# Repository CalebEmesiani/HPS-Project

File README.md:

# HPS-Project
 My project for the Google Hardware Product Sprint

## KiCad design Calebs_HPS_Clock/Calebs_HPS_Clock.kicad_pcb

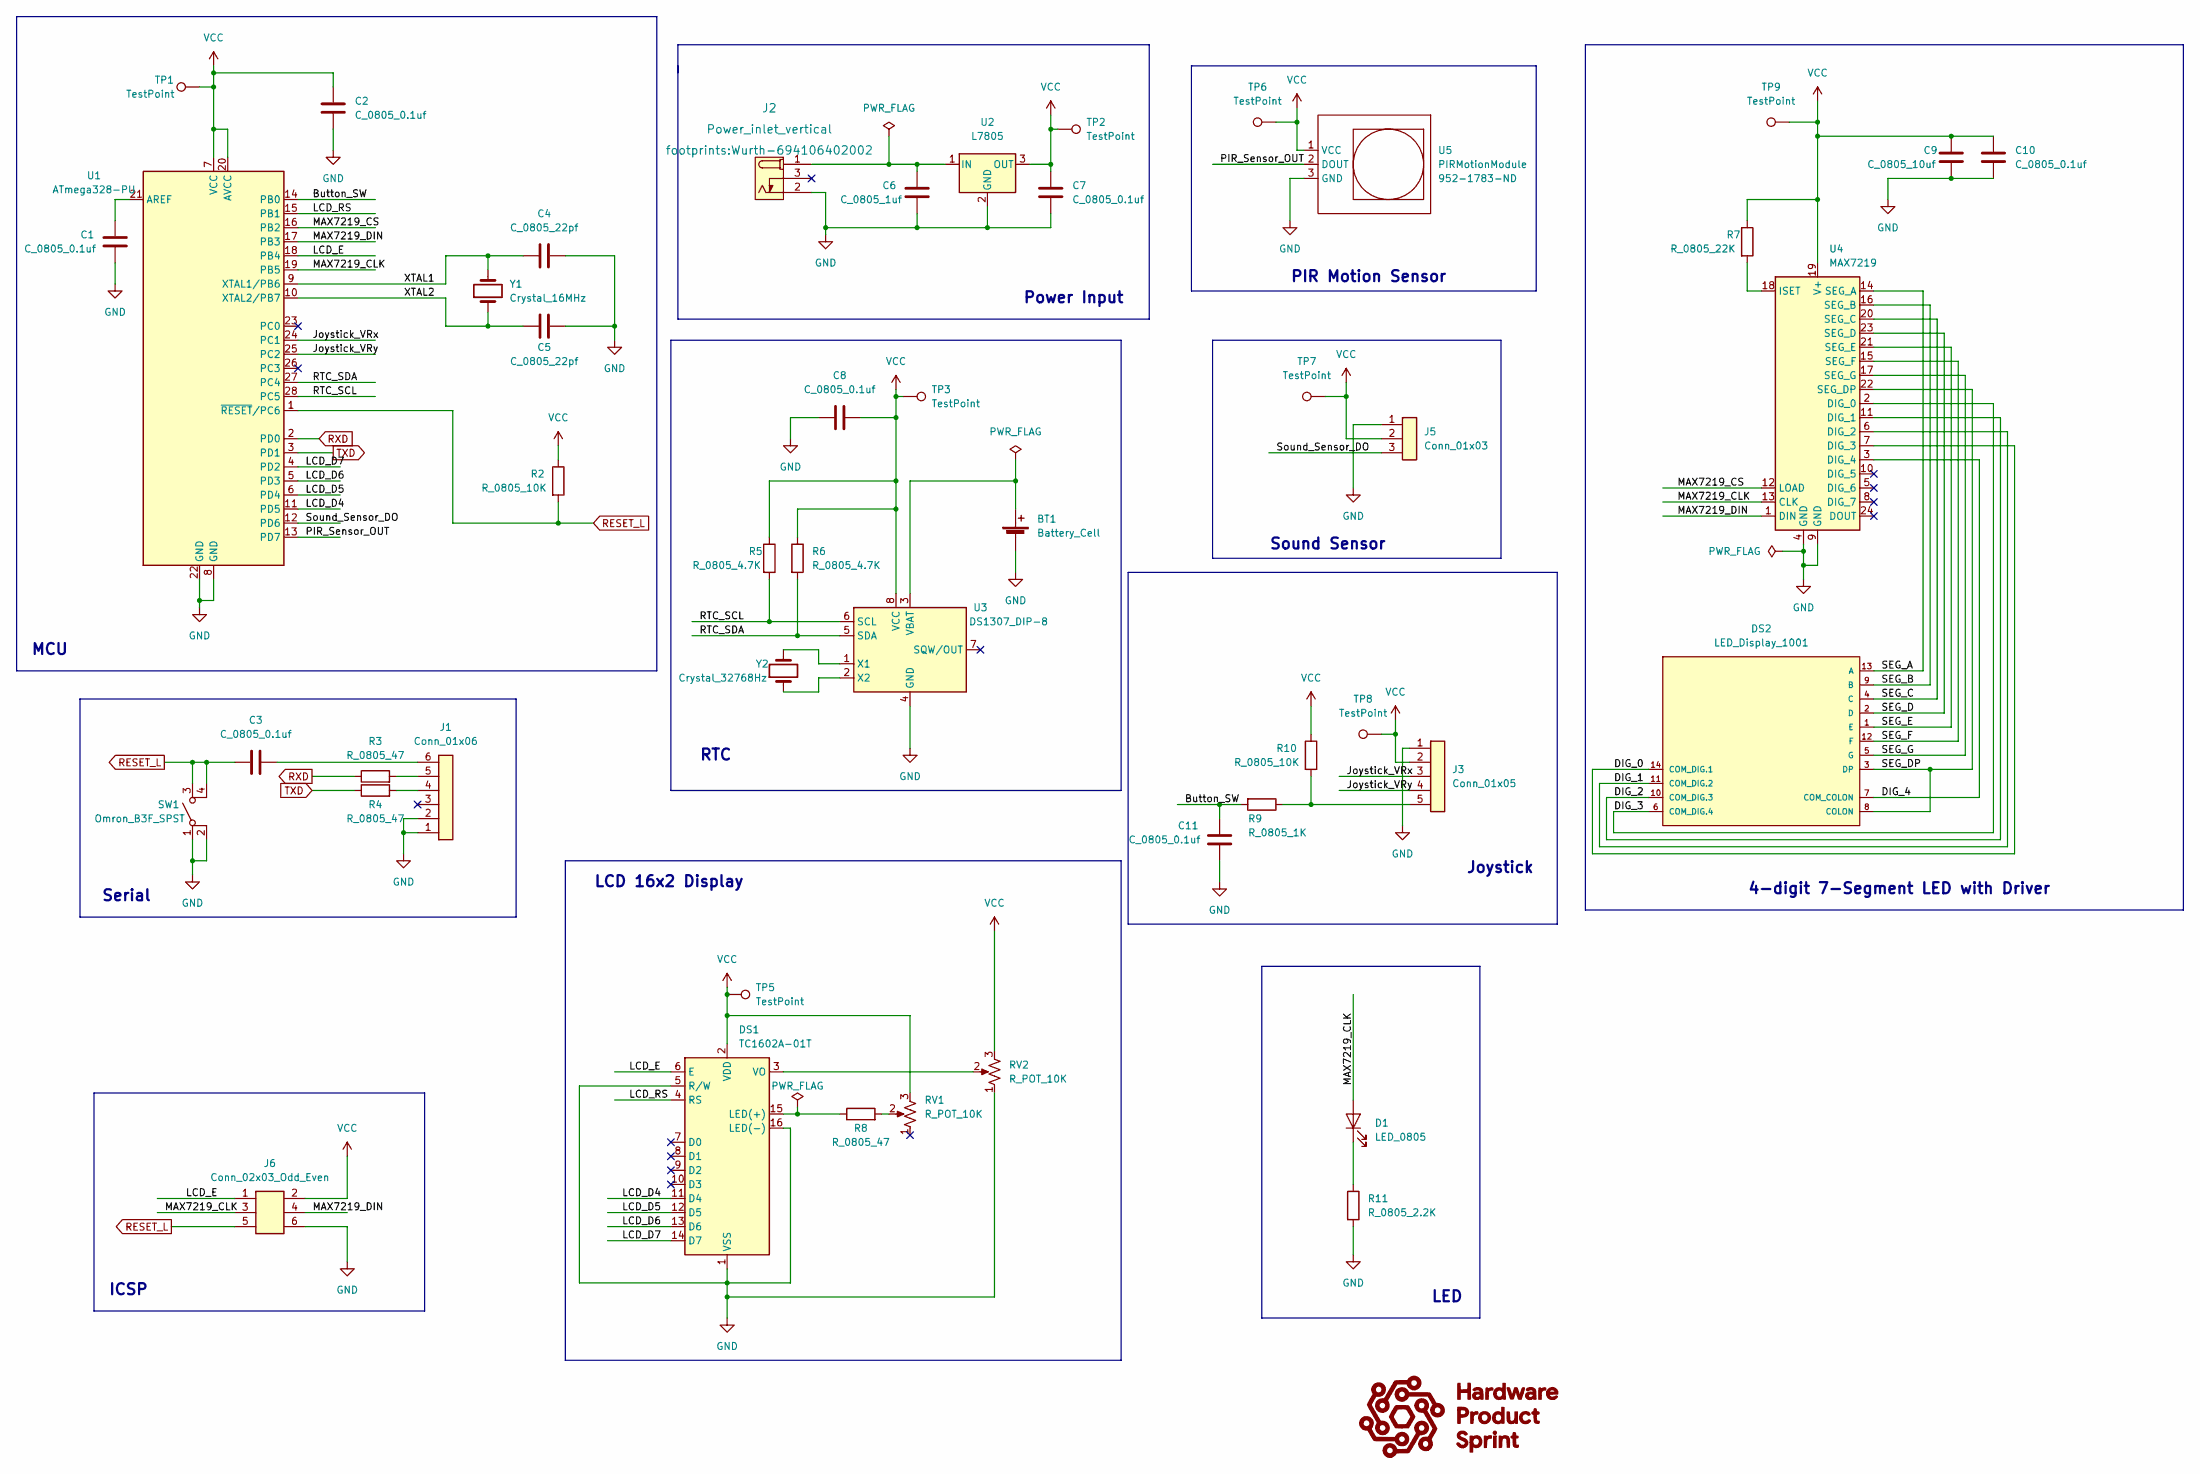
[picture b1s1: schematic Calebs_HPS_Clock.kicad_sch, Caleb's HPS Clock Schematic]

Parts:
BT1: Battery_Cell; BatteryHolder_Keystone_106_1x20mm; MPN BS-7; Digikey PN BS-7-ND
C1, C2, C3, C7, C8, C10, C11: C_0805_0.1uf; C_0805_2012Metric; Voltage N/A; Tolerance N/A; MPN 08055C104KAT2A; Digikey PN 478-1395-1-ND
C4, C5: C_0805_22pf; C_0805_2012Metric; Voltage N/A; Tolerance N/A; MPN CC0805JRNPO9BN220; Digikey PN 311-1103-1-ND
C6: C_0805_1uf; C_0805_2012Metric; Voltage N/A; Tolerance N/A; MPN CC0805KKX7R8BB105; Digikey PN 311-1456-1-ND
C9: C_0805_10uf; C_0805_2012Metric; Voltage N/A; Tolerance N/A; MPN GRM21BR61E106KA73L; Digikey PN 490-5523-1-ND
D1: LED_0805; LED_0805_2012Metric; MPN 150080RS75000; Digikey PN 732-4984-1-ND
DS1: TC1602A-01T; MPN 1447; Digikey PN 1528-2212-ND
DS2: LED_Display_1001; Adafruit-1001-0-0-MFG; forward voltage 3.2V; reverse voltage 5V; mouser part number 485-1001; digikey description WHITE 7-SEGMENT CLOCK DISPLAY
J1: Conn_01x06; PinHeader_1x06_P2.54mm_Vertical; MPN 61300611121; Digikey PN 732-5319-ND
J2: Power_inlet_vertical; Wurth-694106402002; MPN 694106402002; Digikey PN 732-5931-ND
J3: Conn_01x05; PinHeader_1x05_P2.54mm_Vertical; MPN 61300511121; Digikey PN 732-5318-ND
J5: Conn_01x03; PinHeader_1x03_P2.54mm_Vertical; MPN 61300311121; Digikey PN 732-5316-ND
J6: Conn_02x03_Odd_Even; PinHeader_2x03_P2.54mm_Vertical; MPN PRPC003DAAN-RC; Digikey PN S2011EC-03-ND
R2, R10: R_0805_10K; R_0805_2012Metric; Tolerance N/A; MPN RC0805FR-0710KL; Digikey PN 311-10.0KCRCT-ND
R3, R4, R8: R_0805_47; R_0805_2012Metric; Tolerance N/A; Mouser PN N/A; Digikey PN RC0805FR-0747RL
R5, R6: R_0805_4.7K; R_0805_2012Metric; Tolerance N/A; MPN RC0805FR-074K7L; Digikey PN 311-4.70KCRCT-ND
R7: R_0805_22K; R_0805_2012Metric; Tolerance N/A; MPN RC0805FR-0722KL; Digikey PN 311-22.0KCRCT-ND
R9: R_0805_1K; R_0805_2012Metric; Tolerance N/A; Mouser PN N/A; Digikey PN RC0805FR-0710KL
R11: R_0805_2.2K; R_0805_2012Metric; Tolerance N/A; MPN N/A; Digikey PN 311-2.20KCRCT-ND
RV1, RV2: R_POT_10K; Potentiometer_Bourns_3386P_Vertical; MPN 3386P-1-103TLF; Digikey PN 3386P-103TLF-ND
SW1: Omron_B3F_SPST; SW_SPST_Omron_B3FS-100xP; MPN B3FS-1000P; Digikey PN SW423CT-ND
TP1, TP2, TP3, TP5, TP6, TP7, TP8, TP9: TestPoint; TestPoint_THTPad_D2.0mm_Drill1.0mm
U1: ATmega328-PU; DIP-28_W7.62mm; MPN ED281DT; Digikey PN ED3050-5-ND
U2: L7805; TO-252-2; MPN L7805CDT-TR; Digikey PN 497-7255-1-ND
U3: DS1307_DIP-8; DIP-8_W7.62mm; MPN A 08-LC-TT; Digikey PN AE9986-ND
U4: MAX7219; DIP-24_W7.62mm; MPN ED241DT; Digikey PN ED3049-5-ND
U5: PIRMotionModule; Digikey PN 952-1783-ND
Y1: Crystal_16MHz; Crystal_SMD_HC49-SD; MPN ECS-160-20-5PXDN-TR; Digikey PN XC1299CT-ND
Y2: Crystal_32768Hz; Crystal_SMD_2Pin_3.2x1.5mm; MPN Q 0,032768-JTX310-12,5-20-T1-HMR-50K-LF; Digikey PN 1908-1314-1-ND

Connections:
/Button_SW: C11.1, R9.2, U1.14 (PB0)
/DIG_0: DS2.14 (COM_DIG.1), U4.7 (DIG_3)
/DIG_1: DS2.11 (COM_DIG.2), U4.6 (DIG_2)
/DIG_2: DS2.10 (COM_DIG.3), U4.11 (DIG_1)
/DIG_3: DS2.6 (COM_DIG.4), U4.2 (DIG_0)
/DIG_4: DS2.7 (COM_COLON), U4.3 (DIG_4)
/Joystick_VRx: J3.3, U1.24 (PC1)
/Joystick_VRy: J3.4, U1.25 (PC2)
/LCD_D4: DS1.11 (D4), U1.11 (PD5)
/LCD_D5: DS1.12 (D5), U1.6 (PD4)
/LCD_D6: DS1.13 (D6), U1.5 (PD3)
/LCD_D7: DS1.14 (D7), U1.4 (PD2)
/LCD_E: DS1.6 (E), J6.1, U1.18 (PB4)
/LCD_RS: DS1.4 (RS), U1.15 (PB1)
/MAX7219_CLK: D1.2 (A), J6.3, U1.19 (PB5), U4.13 (CLK)
/MAX7219_CS: U1.16 (PB2), U4.12 (LOAD)
/MAX7219_DIN: J6.4, U1.17 (PB3), U4.1 (DIN)
/PIR_Sensor_OUT: U1.13 (PD7), U5.2 (DOUT)
/RTC_SCL: R5.2, U1.28 (PC5), U3.6 (SCL)
/RTC_SDA: R6.2, U1.27 (PC4), U3.5 (SDA)
/SEG_A: DS2.13 (A), U4.14 (SEG_A)
/SEG_B: DS2.9 (B), U4.16 (SEG_B)
/SEG_C: DS2.4 (C), U4.20 (SEG_C)
/SEG_D: DS2.2 (D), U4.23 (SEG_D)
/SEG_DP: DS2.3 (DP), DS2.8 (COLON), U4.22 (SEG_DP)
/SEG_E: DS2.1 (E), U4.21 (SEG_E)
/SEG_F: DS2.12 (F), U4.15 (SEG_F)
/SEG_G: DS2.5 (G), U4.17 (SEG_G)
/Sound_Sensor_DO: J5.3, U1.12 (PD6)
/XTAL1: C4.1, U1.9 (XTAL1/PB6), Y1.2
/XTAL2: C5.1, U1.10 (XTAL2/PB7), Y1.1
GND: BT1.2 (-), C1.2, C2.2, C4.2, C5.2, C6.2, C7.2, C8.1, C9.2, C10.2, C11.2, DS1.1 (VSS), DS1.5 (R/W), DS1.16 (LED(-)), J1.1, J1.2, J2.2 (OUT), J3.1, J5.1, J6.6, R11.2, RV2.1, SW1.1 (A), SW1.2 (A), U1.8 (GND), U1.22 (GND), U2.2 (GND), U3.4 (GND), U4.4 (GND), U4.9 (GND), U5.3 (GND)
unnamed: BT1.1 (+), U3.3 (VBAT)
unnamed: C1.1, U1.21 (AREF)
unnamed: C3.2, J1.6
unnamed: C6.1, J2.1 (POLE), U2.1 (IN)
unnamed: D1.1 (K), R11.1
unnamed: DS1.3 (VO), RV2.2
unnamed: DS1.15 (LED(+)), R8.1
unnamed: J1.4, R4.2
unnamed: J1.5, R3.2
unnamed: J3.5, R9.1, R10.2
unnamed: R7.2, U4.18 (ISET)
unnamed: R8.2, RV1.2
unnamed: U3.1 (X1), Y2.2
unnamed: U3.2 (X2), Y2.1
RESET_L: C3.1, J6.5, R2.2, SW1.3 (B), SW1.4 (B), U1.1 (~RESET/PC6)
RXD: R3.1, U1.2 (PD0)
TXD: R4.1, U1.3 (PD1)
VCC: C2.1, C7.1, C8.2, C9.1, C10.1, DS1.2 (VDD), J3.2, J5.2, J6.2, R2.1, R5.1, R6.1, R7.1, R10.1, RV1.3, RV2.3, TP1.1, TP2.1, TP3.1, TP5.1, TP6.1, TP7.1, TP8.1, TP9.1, U1.7 (VCC), U1.20 (AVCC), U2.3 (OUT), U3.8 (VCC), U4.19 (V+), U5.1 (VCC)

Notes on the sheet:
RTC
LCD 16x2 Display
ICSP
Joystick
LED
MCU
4-digit 7-Segment LED with Driver
Power Input
Sound Sensor
Serial
PIR Motion Sensor

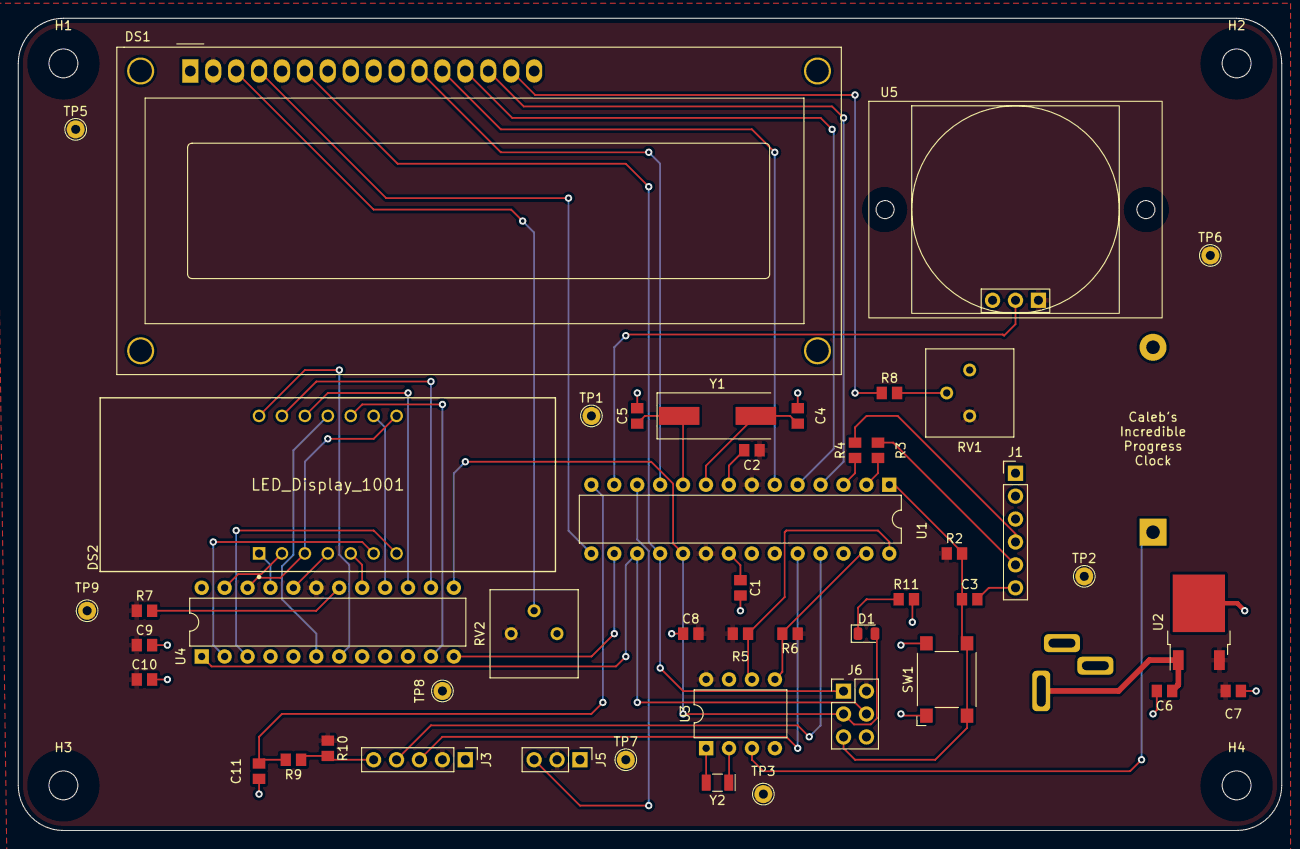
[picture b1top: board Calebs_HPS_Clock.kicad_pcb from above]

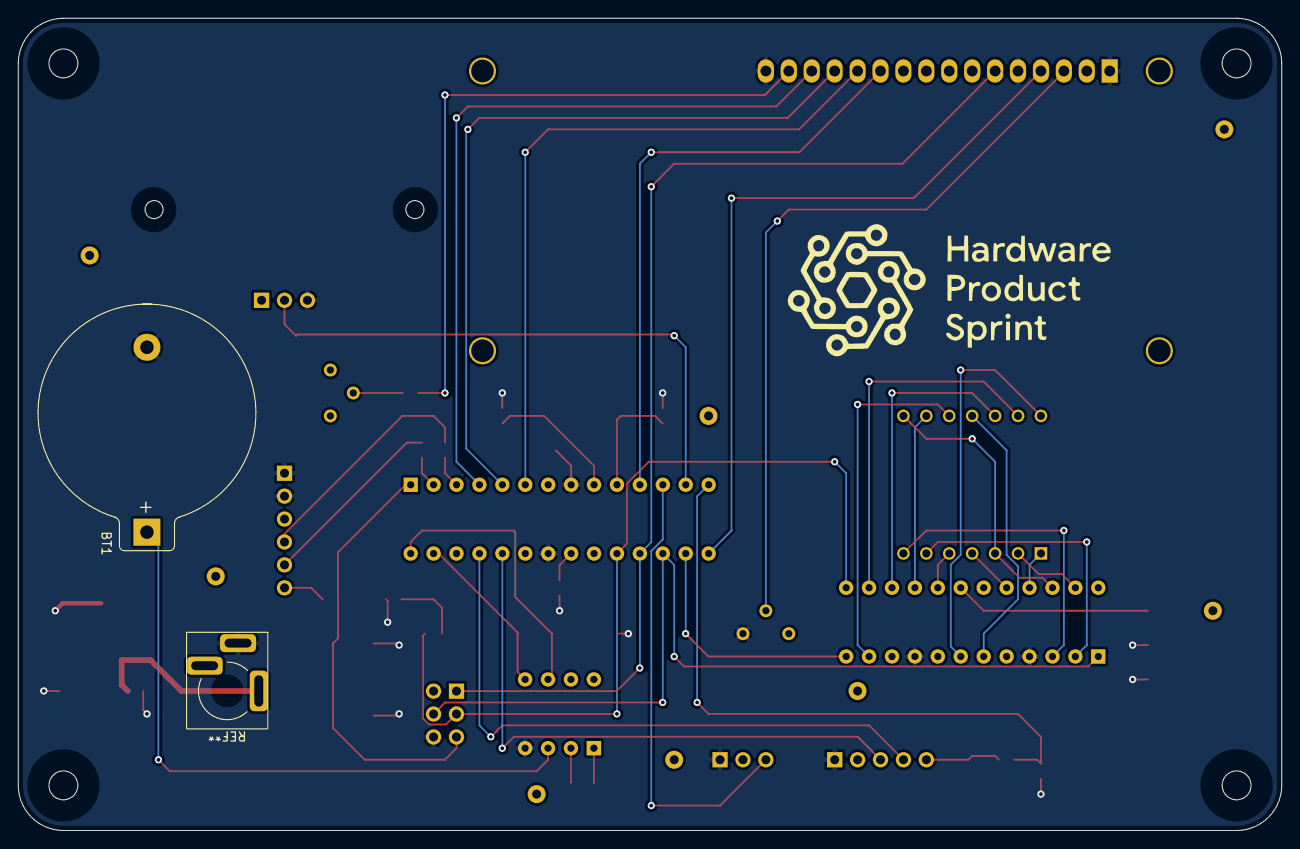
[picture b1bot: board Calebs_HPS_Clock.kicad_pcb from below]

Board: 2 copper layers, 140.0 x 90.0 mm, 52 parts (2 on the bottom side), 50 nets.

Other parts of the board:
H1, H2, H3, H4: MountingHole; MountingHole_3.2mm_M3

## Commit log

2023-07-24 Initial Design Commit
2023-07-24 Adding KiCad libraries
2023-07-24 PCB Update
